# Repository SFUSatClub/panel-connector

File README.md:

# panel-connector
KiCad project of the connector board connecting the 4 outer panels to the internal PC104 stackup.

This repository uses the SFU Satellite Team's KiCad component library as a submodule.
To start working on the repository:

```
1. Open the git shell
2. Navigate to the directory you wish to place the repository inside
3. git clone --recursive "https://github.com/SFUSatClub/panel-connector.git"
4. cd .\panel-connector\KiCad-Lib\
5. git checkout master
```

If you modify either the component schematic or footprint libraries you must push those changes to the SFUSatClub/KiCad-Lib repository.

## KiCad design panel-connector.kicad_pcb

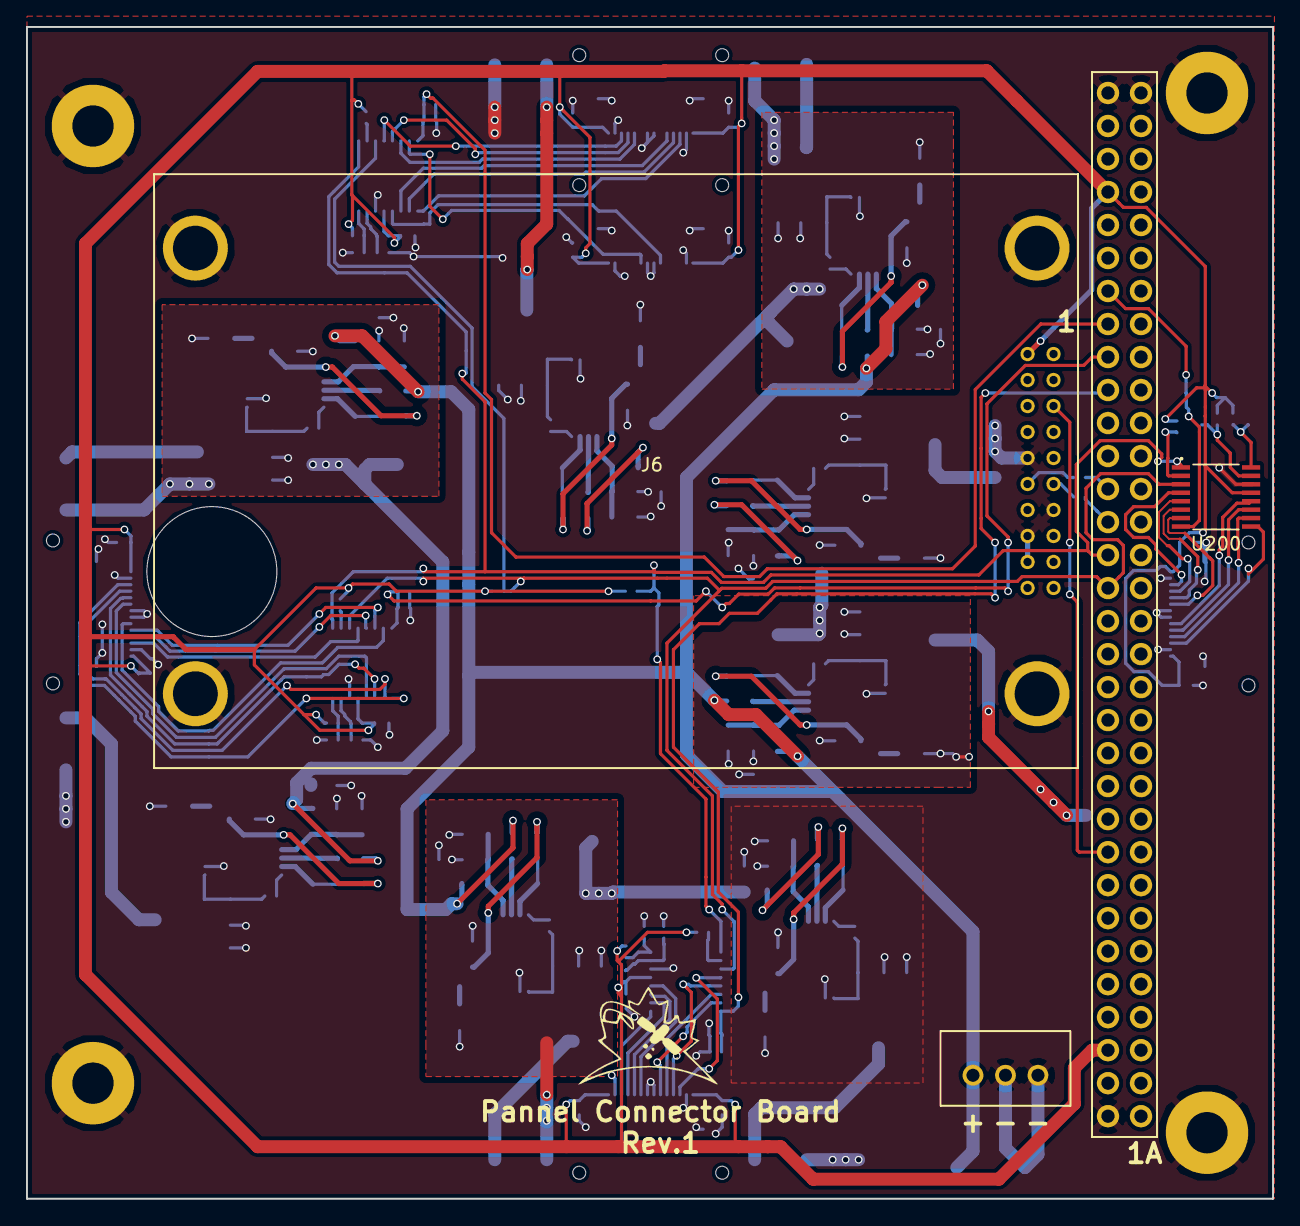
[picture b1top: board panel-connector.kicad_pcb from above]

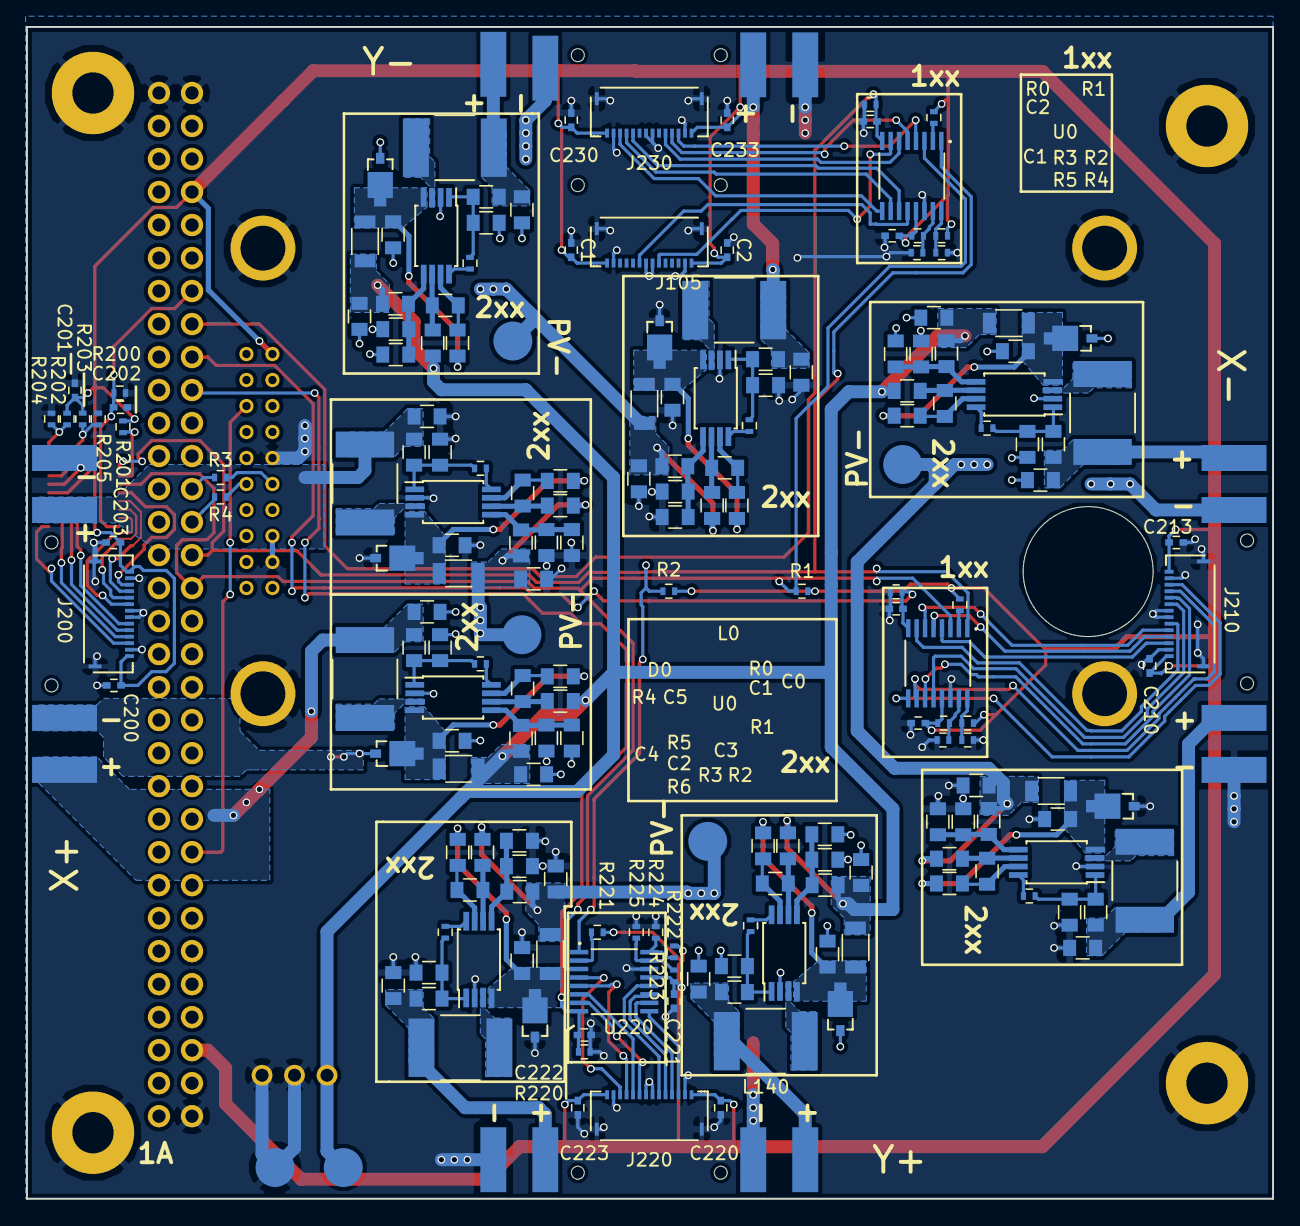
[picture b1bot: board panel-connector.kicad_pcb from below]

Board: 2 copper layers, 95.9 x 90.2 mm, 212 parts (204 on the bottom side), 120 nets.

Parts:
C1, C2, C200, C201, C202, C203, C210, C211, C212, C213, C220, C221, C222, C223, C230, C231, C232, C233: DNP; C_0402
C100, C104, C110, C114, C120, C124, C130, C134, C140, C144, C150, C154, C160, C164, C170, C174: 10uF; C_0805
C101, C111, C121, C131, C141, C151, C161, C171: 100nF; C_0805
C102, C112, C122, C132, C142, C152, C162, C172: 1n0F; C_0805
C103, C113, C123, C133, C143, C153, C163, C173: 1u0F; C_0805
C105, C115, C125, C135, C145, C155, C165, C175: 4u7F; C_0805
D100, D110, D120, D130, D140, D150, D160, D170: SMM4F5.0A-TR; SMM4F
J1: PC104-8BIT; PC104-8bit
J2, J3, J4, J5: PC104PTH
J6: OEM719
J7: B3B-XH-A(LF)(SN); B3B-XH-A
J8, J9, J10, J11, J12, J13: TEST_1P; Measurement_Point_Round-SMD-Pad_Big
J105, J200, J210, J220, J230: MOLEX_FFC-14
J201, J202, J203, J204, J211, J212, J213, J214, J221, J222, J223, J224, J231, J232, J233, J234: CONN-TAB; CONN_TAB
L100, L110, L120, L130, L140, L150, L160, L170: L_10u0_10%_1.42A_2-SMD,; L_2220
R1, R2, R200, R202, R203, R210, R213, R214, R220, R222, R225, R230, R234, R235: DNP; R_0402
R3, R4, R101, R111, R121, R131, R141, R151, R161, R171, R201, R204, R205, R211, R212, R215, R221, R223, R224, R231, R232, R233: 0R; R_0402
R100, R110, R120, R130, R140, R150, R160, R170: 1K; R_0805
R102, R103, R112, R113, R122, R123, R132, R133, R142, R143, R152, R153, R162, R163, R172, R173: 1k0; R_0805
R104, R114, R124, R134, R144, R154, R164, R174: 10m0; R_1206
R105, R115, R125, R135, R145, R155, R165, R175: 1M0; R_0805
R106, R116, R126, R136, R146, R156, R166, R176: 357k; R_0805
U100, U110, U120, U130, U140, U150, U160, U170: SPV1040; TSSOP-8_4.4x3mm_Pitch0.65mm
U200, U210, U220, U230: ADG728; TSSOP-16

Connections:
/3V3: C1.2, C2.2, C200.2, C201.1, C203.1, C210.2, C211.1, C213.1, C220.2, C221.1, C223.1, C230.2, C231.1, C233.1, J1.3B, J1.29B, J6.2, J105.1, J105.14, J200.1, J200.14, J210.1, J210.14, J220.1, J220.14, J230.1, J230.14, R1.1, R2.1, R201.2, R202.1, R203.1, R211.2, R212.1, R213.1, R221.2, R222.1, R223.1, R231.2, R232.1, R233.1, U200.13, U210.13, U220.13, U230.13
/GPS_RST: J1.9B, J6.5
/GPS_RX: J1.20B, R3.1
/GPS_TX: J1.19B, R4.2
/MPPT_X+_1/LX: L100.2, U100.3
/MPPT_X+_1/MPPT_OUT: C105.1, D100.C, R102.1, R104.1, U100.4
/MPPT_X+_1/PV+: C100.1, J203.1, L100.1, R100.1
/MPPT_X+_1/PV-: C100.2, C101.2, C102.2, C104.2, C105.2, C114.1, D100.A, J8.1, J204.1, R106.2, R113.1, R114.2, R115.1, U100.2
/MPPT_X+_1/VOUT+: C104.1, C124.1, C144.1, C164.1, J7.1, J12.1, R103.1, R104.2, R105.1, R123.1, R124.2, R125.1, R143.1, R144.2, R145.1, R163.1, R164.2, R165.1
/MPPT_X+_2/LX: L110.2, U110.3
/MPPT_X+_2/MPPT_OUT: C115.1, D110.C, R112.1, R114.1, U110.4
/MPPT_X+_2/PV+: C110.1, J201.1, L110.1, R110.1
/MPPT_X-_1/LX: L120.2, U120.3
/MPPT_X-_1/MPPT_OUT: C125.1, D120.C, R122.1, R124.1, U120.4
/MPPT_X-_1/PV+: C120.1, J213.1, L120.1, R120.1
/MPPT_X-_1/PV-: C120.2, C121.2, C122.2, C124.2, C125.2, C134.1, D120.A, J9.1, J214.1, R126.2, R133.1, R134.2, R135.1, U120.2
/MPPT_X-_2/LX: L130.2, U130.3
/MPPT_X-_2/MPPT_OUT: C135.1, D130.C, R132.1, R134.1, U130.4
/MPPT_X-_2/PV+: C130.1, J211.1, L130.1, R130.1
/MPPT_Y+_1/LX: L140.2, U140.3
/MPPT_Y+_1/MPPT_OUT: C145.1, D140.C, R142.1, R144.1, U140.4
/MPPT_Y+_1/PV+: C140.1, J223.1, L140.1, R140.1
/MPPT_Y+_1/PV-: C140.2, C141.2, C142.2, C144.2, C145.2, C154.1, D140.A, J11.1, J224.1, R146.2, R153.1, R154.2, R155.1, U140.2
/MPPT_Y+_2/LX: L150.2, U150.3
/MPPT_Y+_2/MPPT_OUT: C155.1, D150.C, R152.1, R154.1, U150.4
/MPPT_Y+_2/PV+: C150.1, J221.1, L150.1, R150.1
/MPPT_Y-_1/LX: L160.2, U160.3
/MPPT_Y-_1/MPPT_OUT: C165.1, D160.C, R162.1, R164.1, U160.4
/MPPT_Y-_1/PV+: C160.1, J231.1, L160.1, R160.1
/MPPT_Y-_1/PV-: C160.2, C161.2, C162.2, C164.2, C165.2, C174.1, D160.A, J10.1, J232.1, R166.2, R173.1, R174.2, R175.1, U160.2
/MPPT_Y-_2/LX: L170.2, U170.3
/MPPT_Y-_2/MPPT_OUT: C175.1, D170.C, R172.1, R174.1, U170.4
/MPPT_Y-_2/PV+: C170.1, J233.1, L170.1, R170.1
/Port_X+/!RESET: R201.1, U200.2
/Port_X+/A0: R202.2, R204.1, U200.16
/Port_X+/A1: R203.2, R205.1, U200.15
/Port_X+/D1: J200.3, U200.4
/Port_X+/D2: J200.4, U200.5
/Port_X+/D3: J200.5, U200.6
/Port_X+/D6: J200.10, U200.11
/Port_X+/D7: J200.11, U200.10
/Port_X+/D8: J200.12, U200.9
/Port_X-/!RESET: R211.1, U210.2
/Port_X-/A0: R212.2, R214.1, U210.16
/Port_X-/A1: R213.2, R215.1, U210.15
/Port_X-/D1: J210.3, U210.4
/Port_X-/D2: J210.4, U210.5
/Port_X-/D3: J210.5, U210.6
/Port_X-/D6: J210.10, U210.11
/Port_X-/D7: J210.11, U210.10
/Port_X-/D8: J210.12, U210.9
/Port_Y+/!RESET: R221.1, U220.2
/Port_Y+/A0: R222.2, R224.1, U220.16
/Port_Y+/A1: R223.2, R225.1, U220.15
/Port_Y+/D1: J220.3, U220.4
/Port_Y+/D2: J220.4, U220.5
/Port_Y+/D3: J220.5, U220.6
/Port_Y+/D6: J220.10, U220.11
/Port_Y+/D7: J220.11, U220.10
/Port_Y+/D8: J220.12, U220.9
/Port_Y-/!RESET: R231.1, U230.2
/Port_Y-/A0: R232.2, R234.1, U230.16
/Port_Y-/A1: R233.2, R235.1, U230.15
/Port_Y-/D1: J230.3, U230.4
/Port_Y-/D2: J230.4, U230.5
/Port_Y-/D3: J230.5, U230.6
/Port_Y-/D6: J230.10, U230.11
/Port_Y-/D7: J230.11, U230.10
/Port_Y-/D8: J230.12, U230.9
/SCL: J1.18B, R2.2, U200.1, U210.1, U220.1, U230.1
/SDA: J1.17B, R1.2, U200.3, U210.3, U220.3, U230.3
/SENSOR_X+: C202.1, J1.26B, R200.1, U200.8
/SENSOR_X-: C212.1, J1.24B, R210.1, U210.8
/SENSOR_Y+: C222.1, J1.23B, R220.1, U220.8
/SENSOR_Y-: C232.1, J1.25B, R230.1, U230.8
GND: C1.1, C2.1, C110.2, C111.2, C112.2, C114.2, C115.2, C130.2, C131.2, C132.2, C134.2, C135.2, C150.2, C151.2, C152.2, C154.2, C155.2, C170.2, C171.2, C172.2, C174.2, C175.2, C200.1, C201.2, C202.2, C203.2, C210.1, C211.2, C212.2, C213.2, C220.1, C221.2, C222.2, C223.2, C230.1, C231.2, C232.2, C233.2, D110.A, D130.A, D150.A, D170.A, J1.1B, J1.32A, J1.32B, J2.1, J3.1, J4.1, J5.1, J6.10, J6.13, J6.16, J6.18, J7.2, J7.3, J13.1, J105.2, J105.7, J105.8, J105.13, J105.SHLD, J200.2, J200.7, J200.8, J200.13, J200.SHLD, J202.1, J210.2, J210.7, J210.8, J210.13, J210.SHLD, J212.1, J220.2, J220.7, J220.8, J220.13, J220.SHLD, J222.1, J230.2, J230.7, J230.8, J230.13, J230.SHLD, J234.1, R116.2, R136.2, R156.2, R176.2, R200.2, R204.2, R205.2, R210.2, R214.2, R215.2, R220.2, R224.2, R225.2, R230.2, R234.2, R235.2, U110.2, U130.2, U150.2, U170.2, U200.14, U210.14, U220.14, U230.14
unnamed: C101.1, R100.2, R101.2, U100.1
unnamed: C102.1, R105.2, R106.1, U100.5
unnamed: C103.1, R102.2, U100.7
unnamed: C103.2, R103.2, U100.6
unnamed: C111.1, R110.2, R111.2, U110.1
unnamed: C112.1, R115.2, R116.1, U110.5
unnamed: C113.1, R112.2, U110.7
unnamed: C113.2, R113.2, U110.6
unnamed: C121.1, R120.2, R121.2, U120.1
unnamed: C122.1, R125.2, R126.1, U120.5
unnamed: C123.1, R122.2, U120.7
unnamed: C123.2, R123.2, U120.6
unnamed: C131.1, R130.2, R131.2, U130.1
unnamed: C132.1, R135.2, R136.1, U130.5
unnamed: C133.1, R132.2, U130.7
unnamed: C133.2, R133.2, U130.6
unnamed: C141.1, R140.2, R141.2, U140.1
unnamed: C142.1, R145.2, R146.1, U140.5
unnamed: C143.1, R142.2, U140.7
unnamed: C143.2, R143.2, U140.6
unnamed: C151.1, R150.2, R151.2, U150.1
unnamed: C152.1, R155.2, R156.1, U150.5
unnamed: C153.1, R152.2, U150.7
unnamed: C153.2, R153.2, U150.6
unnamed: C161.1, R160.2, R161.2, U160.1
unnamed: C162.1, R165.2, R166.1, U160.5
unnamed: C163.1, R162.2, U160.7
unnamed: C163.2, R163.2, U160.6
unnamed: C171.1, R170.2, R171.2, U170.1
unnamed: C172.1, R175.2, R176.1, U170.5
unnamed: C173.1, R172.2, U170.7
unnamed: C173.2, R173.2, U170.6
unnamed: J6.11, R4.1
unnamed: J6.12, R3.2
unnamed: R101.1, U100.8
unnamed: R111.1, U110.8
unnamed: R121.1, U120.8
unnamed: R131.1, U130.8
unnamed: R141.1, U140.8
unnamed: R151.1, U150.8
unnamed: R161.1, U160.8
unnamed: R171.1, U170.8
Z+D_A: J105.6, J200.6, J210.6, J220.6, J230.6, U200.7, U210.7, U220.7, U230.7
Z+D_B: J105.9, J200.9, J210.9, J220.9, J230.9, U200.12, U210.12, U220.12, U230.12

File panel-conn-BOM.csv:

reference,name,Digikey PN,number
"R224,R3,R201,R211,R221,R231,R101,R111,R121 R223,R232,R233,R212,R215,R204,R205,R4,R131,R2*1,R1*1",0R,311-0.0LBCT-ND,21
J7,B3B-XH-A(LF)(SN),455-2248-ND,1
J7,B3B-XH-A(LF)(SN) mating,455-2219-ND,1
"J105,J2*0",MOLEX_FFC-14,WM1442CT-ND,6
U2*0,ADG728,ADG728BRUZ-ND,4
U1*0,SPV1040,497-11417-ND,8
L1*0,"L_10u0_10%_1.42A_2-SMD,",495-5656-1-ND,8
R1*5,1M0,RG20P1.0MBCT-ND,8
D1*0,SMM4F5.0A-TR,497-15660-1-ND,8
C1*5,4u7F,587-1302-1-ND,8
"C1*4,C1*0",10uF,445-7658-1-ND,16
R1*4,10m0,WSLP-.01CT-ND,8
"R1*2, R1*3, R1*0",1k0,RG20P1.0KBCT-ND,24
"C1*3, C1*2",1u0F,445-1358-1-ND,16
C1*1,100nF,445-14401-1-ND,8
R1*6,357k,P357KDACT-ND,8

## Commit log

2018-02-04 The real first commit
2018-02-04 Deleting submodule
2018-02-04 Readded submodule
2018-02-04 Added mux
2018-02-05 Added MPPT circuit. MPPT circuit copied from EPS board. MPPT on EPS board should be deleted. Should the negative output of the MPPT circuit be connected to ground or segregated?
2018-02-16 Assigned some footprints and connected some nets
2018-02-18 Begand layout of connectors and added 3d models. The +Z connector will be placed only on the -X side of the board but because of the schematic hierarchy the net shows it is connected to all sides; ig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
2018-02-18 populated mppt schematic and layed out mppt circuit
2018-02-22 Added decoupling to connector
2018-02-25 layed out MPPT
2018-02-26 generated 3d model with gps
2018-02-26 added 3d models
2018-03-04 placed mppt circuits
2018-03-11 routing complete except for GPS_RST
2018-03-11 routing complete
2018-03-19 optimized reference layout
2018-03-22 moved DC connection to eps board inorder to avoid RBF switch above on the eps board
2018-03-22 generated gerbers
2018-03-22 fixed 3v3 trace collision and GPS PTH grounded
2018-03-22 added production doc
2018-04-21 solder mask fixed to conform to min 150um webbing requirement
2018-04-21 added file that should have been in previous commit
2018-06-02 updated pdf
